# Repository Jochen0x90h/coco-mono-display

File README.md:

# CoCo Monochrome Display

Monochrome (1 bit) display module for CoCo

## Import
Add coco-monodisplay/\<version> to your conanfile where version corresponds to a git tag.

## Features
* Support for monochrome displays e.g. 128x64
* I2C and 4-wire SPI
* [SSD1306](https://cdn-shop.adafruit.com/datasheets/SSD1306.pdf)
* [SSD1309](https://www.crystalfontz.com/controllers/SolomonSystech/SSD1309/)
* Simple immediate mode menu system

## Supported Platforms
See README.md of coco base library

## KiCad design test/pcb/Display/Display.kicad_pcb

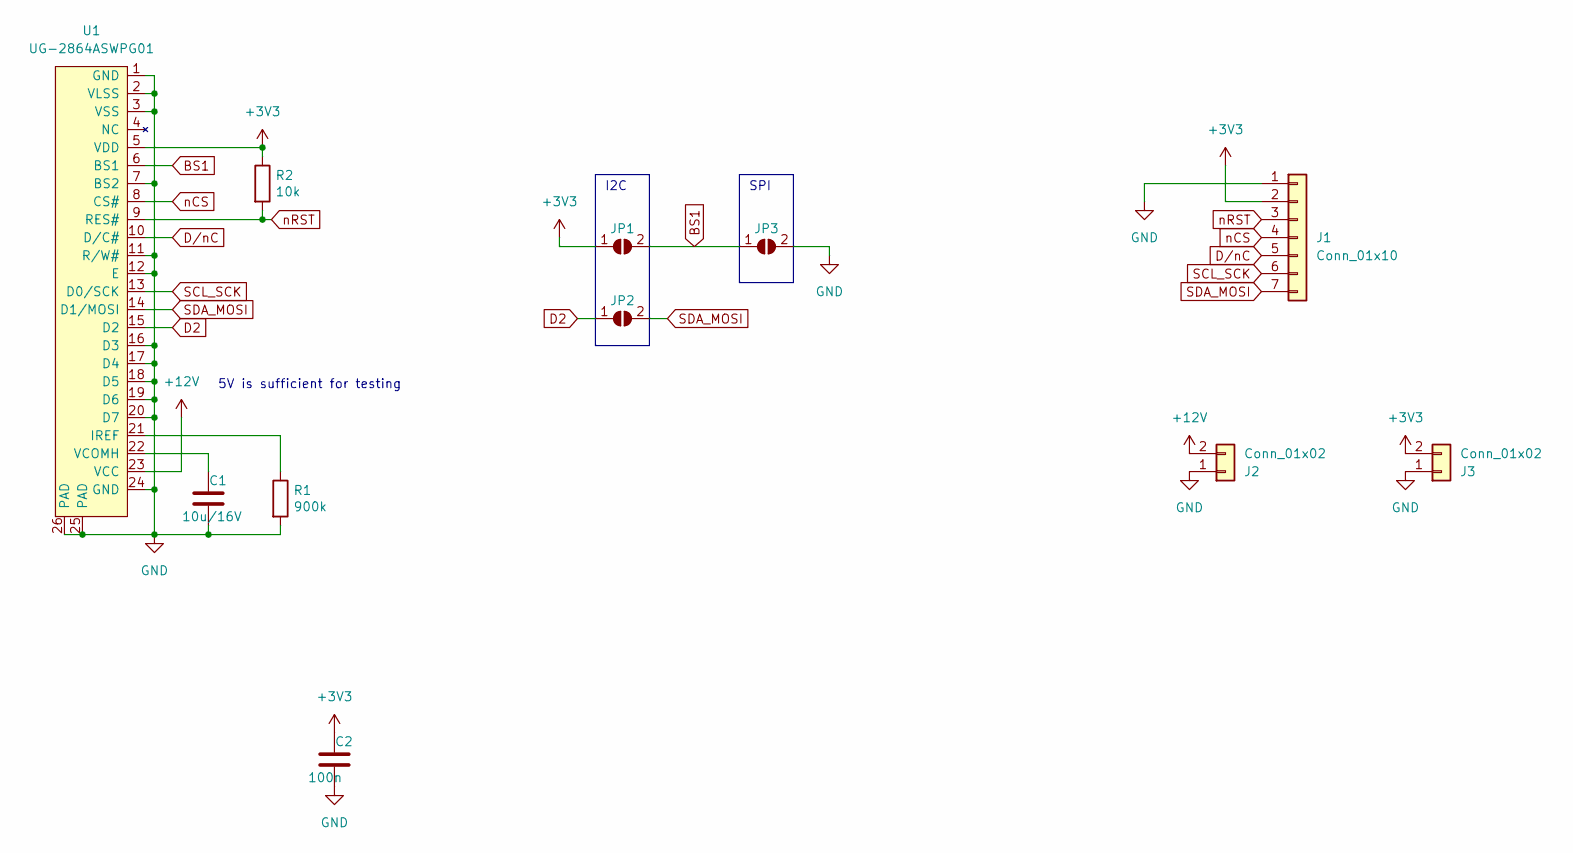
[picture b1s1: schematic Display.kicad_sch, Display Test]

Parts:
C1: 10u/16V; C_1206_3216Metric
C2: 100n; C_0603_1608Metric
J1: Conn_01x10; PinHeader_1x07_P2.54mm_Vertical
J2, J3: Conn_01x02; PinHeader_1x02_P2.54mm_Vertical
JP1, JP2, JP3: SolderJumper_2_Open; Jumper
R1: 900k; R_0603_1608Metric
R2: 10k; R_0603_1608Metric
U1: UG-2864ASWPG01; Connector-Flat-24-0.5mm

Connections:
+3V3: C2.1, J1.2, J3.2, JP1.1 (A), R2.1, U1.5 (VDD)
+12V: J2.2, U1.23 (VCC)
BS1: JP1.2 (B), JP3.1 (A), U1.6 (BS1)
D2: JP2.1 (A), U1.15 (D2)
D/nC: J1.5, U1.10 (D/C#)
GND: C1.2, C2.2, J1.1, J2.1, J3.1, JP3.2 (B), R1.2, U1.1 (GND), U1.2 (VLSS), U1.3 (VSS), U1.7 (BS2), U1.11 (R/W#), U1.12 (E), U1.16 (D3), U1.17 (D4), U1.18 (D5), U1.19 (D6), U1.20 (D7), U1.24 (GND), U1.25 (PAD), U1.26 (PAD)
unnamed: R1.1, U1.21 (IREF)
unnamed: C1.1, U1.22 (VCOMH)
SCL_SCK: J1.6, U1.13 (D0/SCK)
SDA_MOSI: J1.7, JP2.2 (B), U1.14 (D1/MOSI)
nCS: J1.4, U1.8 (CS#)
nRST: J1.3, R2.2, U1.9 (RES#)

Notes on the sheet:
5V is sufficient for testing
SPI
I2C

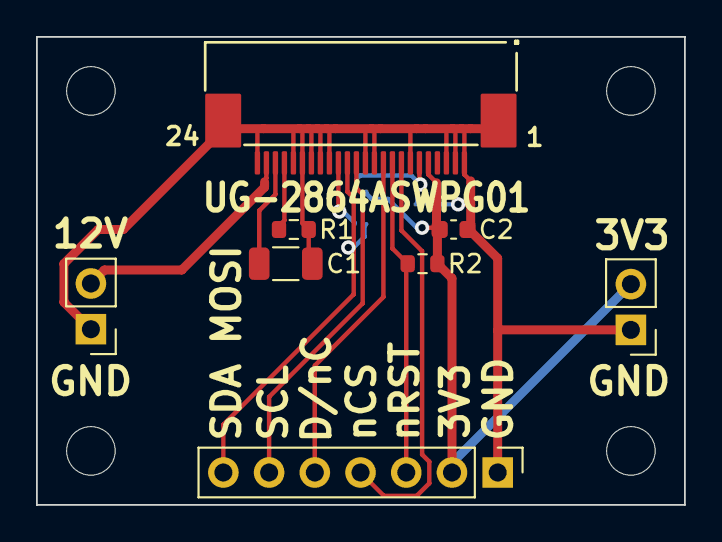
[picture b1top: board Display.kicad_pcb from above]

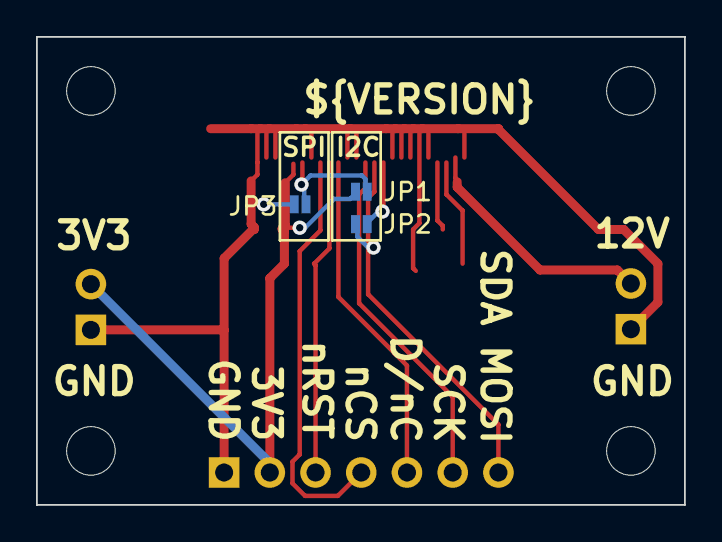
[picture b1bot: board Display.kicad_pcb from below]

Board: 2 copper layers, 36.0 x 26.0 mm, 11 parts (3 on the bottom side), 12 nets.

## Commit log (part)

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2023-08-20 New input paradigm
2023-08-20 New input paradigm (#1)
2024-10-05 Use coco-device/0.3.0
2024-10-05 Use coco-device/0.3.0 (#2)
2026-02-02 Version 0.4.0
2026-02-27 Use steps variable
2026-03-01 Rename test/LedControl to test/LedControl-g431
2026-04-03 Remove need for coco-toolchain
2026-05-22 Use new handers
2026-06-28 Use new TaskList
